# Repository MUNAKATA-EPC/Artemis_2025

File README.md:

# Artemis_2025

宗高アルテミス 2025シーズンリポジトリです。

2025シーズンはSoccer OpenLeagueに出場します。

## リポジトリについて (引用：2024シーズンリポジトリ)
・フォルダ階層をきれいにしよう  
・パス設定は相対パス基準にしよう  
・あとは動けばなんでもよし。  

## 命名規則など (一部引用：2024シーズンリポジトリ)
・各ロボットごとにプロジェクトファイルを作成しましょう。(英字表記推奨、フォルダ名に2バイト文字は嫌じゃ！！！！)  
　ex. Project_hogehugaNode

・PlatformIO等で作成されたプロジェクトフォルダの名前は (プロジェクト名)-(開発環境) にしましょう。  
　ex. hogehoge-teensy40 hugahuga-seeeduinoxiaorp2040
 
・KiCad、Fusion360などで作成されたフォルダ、ファイルの名前は一目でわかる名前にしましょう。  
　間違ってもファイル名を"unko"とかにするなよ！！！！！(戒め)

 ## 開発環境
 |種類|使用ソフト|
 |:---:|:---|
 |機体設計|Autodesk Fusion|
 |回路設計|KiCad 7.x (only use 7.x ver.)|
 |ソフト開発|Microsoft Visual Studio Code (with PlatformIO)<br>Arduino IDE<br>OpenMV IDE|

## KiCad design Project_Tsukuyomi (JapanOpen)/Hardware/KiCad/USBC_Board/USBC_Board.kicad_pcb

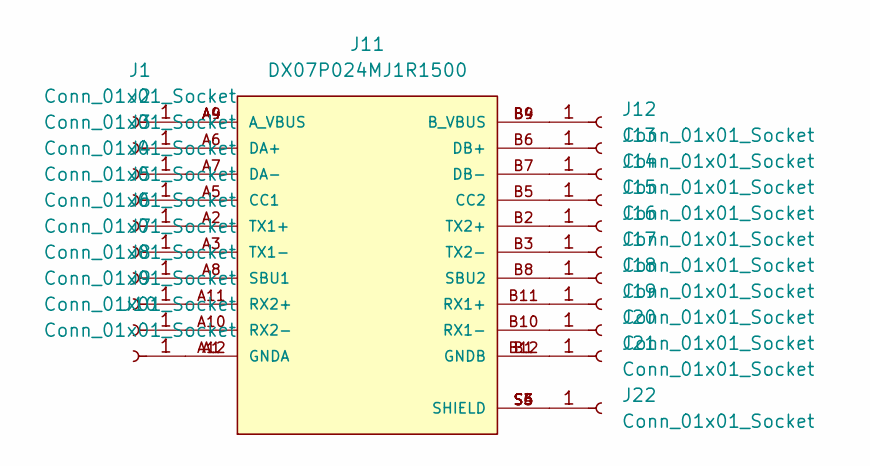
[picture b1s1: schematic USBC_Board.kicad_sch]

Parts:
J1, J2, J3, J4, J5, J6, J7, J8, J9, J10, J12, J13, J14, J15, J16, J17, J18, J19, J20, J21, J22: Conn_01x01_Socket; TestPoint_Pad_D1.0mm
J11: DX07P024MJ1R1500; JAE_DX07P024MJ1R1500; PARTREV 1.0; LCSC C134112

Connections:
unnamed: J1.1, J11.A4 (A_VBUS), J11.A9 (A_VBUS)
unnamed: J10.1, J11.A1 (GNDA), J11.A12 (GNDA)
unnamed: J4.1, J11.A5 (CC1)
unnamed: J11.B5 (CC2), J15.1
unnamed: J2.1, J11.A6 (DA+)
unnamed: J3.1, J11.A7 (DA-)
unnamed: J11.B6 (DB+), J13.1
unnamed: J11.B7 (DB-), J14.1
unnamed: J11.B11 (RX1+), J19.1
unnamed: J11.B10 (RX1-), J20.1
unnamed: J8.1, J11.A11 (RX2+)
unnamed: J9.1, J11.A10 (RX2-)
unnamed: J7.1, J11.A8 (SBU1)
unnamed: J11.B8 (SBU2), J18.1
unnamed: J5.1, J11.A2 (TX1+)
unnamed: J6.1, J11.A3 (TX1-)
unnamed: J11.B2 (TX2+), J16.1
unnamed: J11.B3 (TX2-), J17.1
unnamed: J11.B4 (B_VBUS), J11.B9 (B_VBUS), J12.1
unnamed: J11.B1 (GNDB), J11.B12 (GNDB), J21.1
unnamed: J11.S3 (SHIELD), J11.S4 (SHIELD), J11.S5 (SHIELD), J11.S6 (SHIELD), J22.1

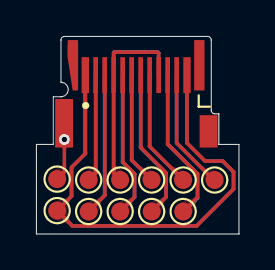
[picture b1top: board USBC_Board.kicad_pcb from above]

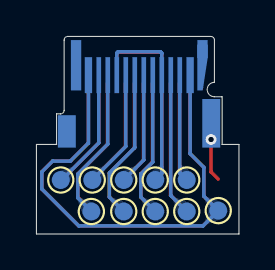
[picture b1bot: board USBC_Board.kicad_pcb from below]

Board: 2 copper layers, 11.2 x 11.0 mm, 22 parts (10 on the bottom side), 21 nets.

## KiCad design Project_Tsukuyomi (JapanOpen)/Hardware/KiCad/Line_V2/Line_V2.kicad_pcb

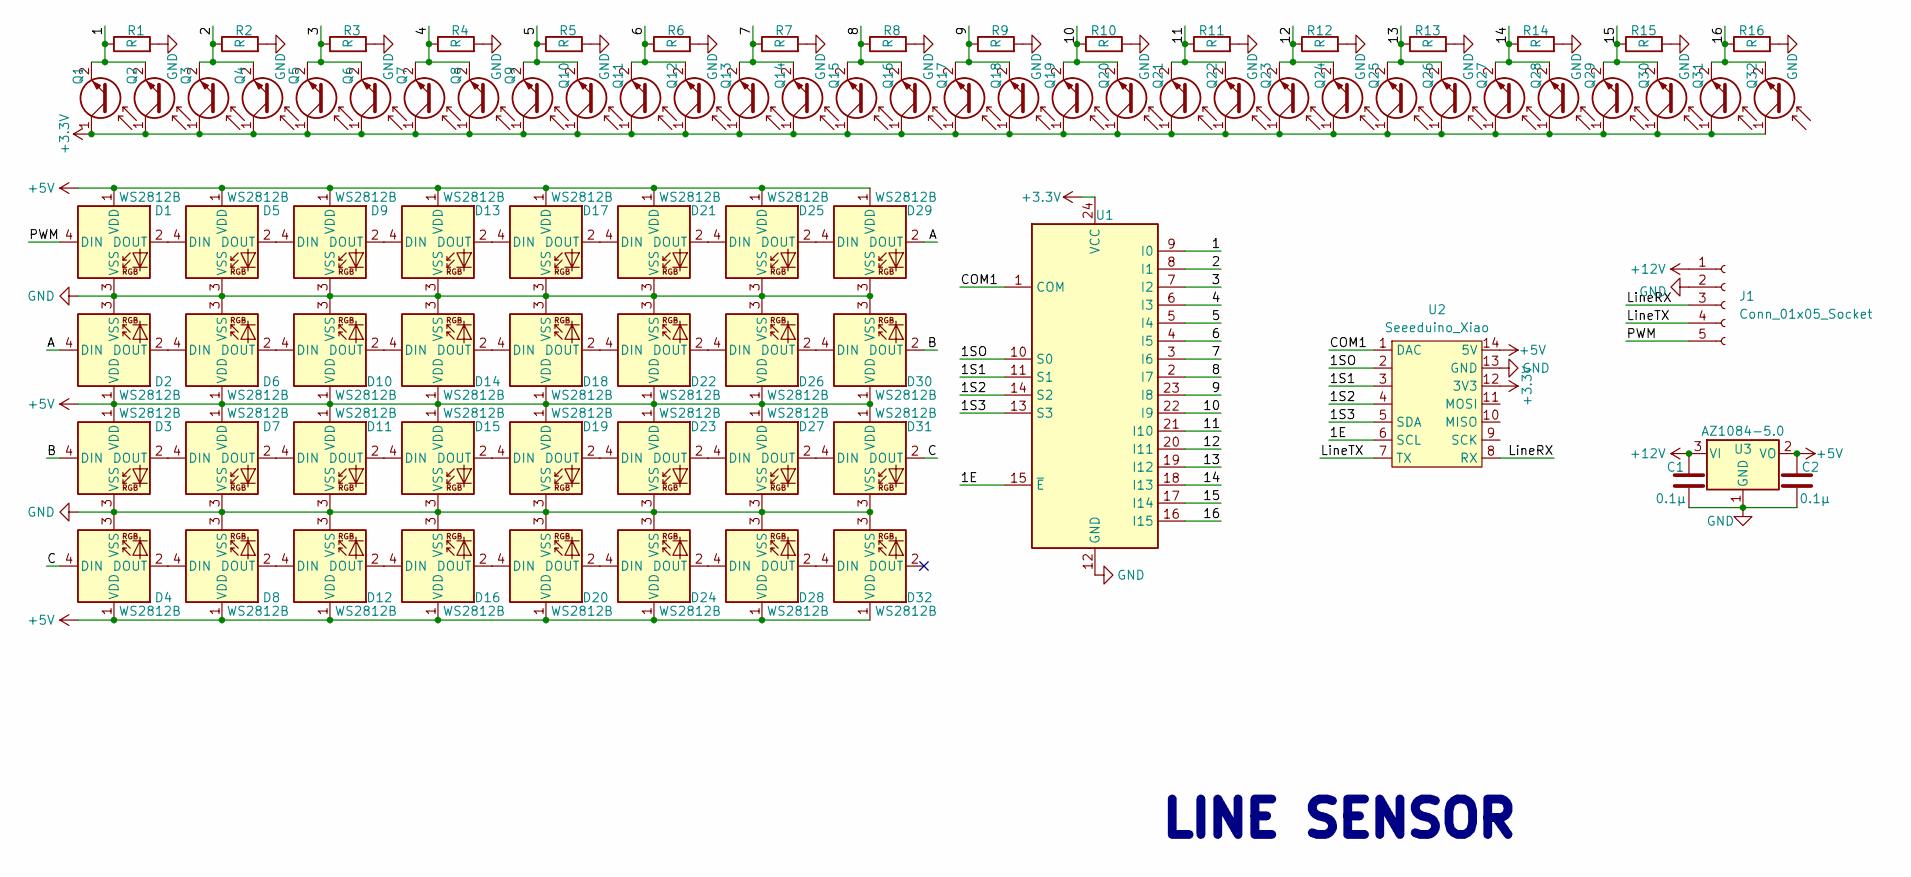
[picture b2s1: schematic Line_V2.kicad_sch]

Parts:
C1: 0.1μ; C_1210_3225Metric
C2: 0.1μ; C_0402_1005Metric; LCSC C1525
D1, D2, D3, D4, D5, D6, D7, D8, D9, D10, D11, D12, D13, D14, D15, D16, D17, D18, D19, D20, D21, D22, D23, D24, D25, D26, D27, D28, D29, D30, D31, D32: WS2812B; LED_WS2812B_PLCC4_5.0x5.0mm_P3.2mm; LCSC C965555
J1: Conn_01x05_Socket; PinHeader_1x05_P2.54mm_Vertical
Q1, Q2, Q3, Q4, Q5, Q6, Q7, Q8, Q9, Q10, Q11, Q12, Q13, Q14, Q15, Q16, Q17, Q18, Q19, Q20, Q21, Q22, Q23, Q24, Q25, Q26, Q27, Q28, Q29, Q30, Q31, Q32: Q_Photo_NPN; LED_D3.0mm
R1, R2, R3, R4, R5, R6, R7, R8, R9, R10, R11, R12, R13, R14, R15, R16: R; R_0603_1608Metric; LCSC C912493
U1: CD74HC4067SM; SSOP-24_5.3x8.2mm_P0.65mm; LCSC C98457
U2: Seeeduino_Xiao; seeeduinoXIAO
U3: AZ1084-5.0; TO-252-2

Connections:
+3.3V: Q1.1 (C), Q2.1 (C), Q3.1 (C), Q4.1 (C), Q5.1 (C), Q6.1 (C), Q7.1 (C), Q8.1 (C), Q9.1 (C), Q10.1 (C), Q11.1 (C), Q12.1 (C), Q13.1 (C), Q14.1 (C), Q15.1 (C), Q16.1 (C), Q17.1 (C), Q18.1 (C), Q19.1 (C), Q20.1 (C), Q21.1 (C), Q22.1 (C), Q23.1 (C), Q24.1 (C), Q25.1 (C), Q26.1 (C), Q27.1 (C), Q28.1 (C), Q29.1 (C), Q30.1 (C), Q31.1 (C), Q32.1 (C), U1.24 (VCC), U2.12 (3V3)
+5V: C2.2, D1.1 (VDD), D2.1 (VDD), D3.1 (VDD), D4.1 (VDD), D5.1 (VDD), D6.1 (VDD), D7.1 (VDD), D8.1 (VDD), D9.1 (VDD), D10.1 (VDD), D11.1 (VDD), D12.1 (VDD), D13.1 (VDD), D14.1 (VDD), D15.1 (VDD), D16.1 (VDD), D17.1 (VDD), D18.1 (VDD), D19.1 (VDD), D20.1 (VDD), D21.1 (VDD), D22.1 (VDD), D23.1 (VDD), D24.1 (VDD), D25.1 (VDD), D26.1 (VDD), D27.1 (VDD), D28.1 (VDD), D29.1 (VDD), D30.1 (VDD), D31.1 (VDD), D32.1 (VDD), U2.14 (5V), U3.2 (VO)
+12V: C1.2, J1.1, U3.3 (VI)
/1: Q1.2 (E), Q2.2 (E), R1.1, U1.9 (I0)
/1E: U1.15 (~E), U2.6 (SCL)
/1S1: U1.11 (S1), U2.3
/1S2: U1.14 (S2), U2.4
/1S3: U1.13 (S3), U2.5 (SDA)
/1SO: U1.10 (S0), U2.2
/2: Q3.2 (E), Q4.2 (E), R2.1, U1.8 (I1)
/3: Q5.2 (E), Q6.2 (E), R3.1, U1.7 (I2)
/4: Q7.2 (E), Q8.2 (E), R4.1, U1.6 (I3)
/5: Q9.2 (E), Q10.2 (E), R5.1, U1.5 (I4)
/6: Q11.2 (E), Q12.2 (E), R6.1, U1.4 (I5)
/7: Q13.2 (E), Q14.2 (E), R7.1, U1.3 (I6)
/8: Q15.2 (E), Q16.2 (E), R8.1, U1.2 (I7)
/9: Q17.2 (E), Q18.2 (E), R9.1, U1.23 (I8)
/10: Q19.2 (E), Q20.2 (E), R10.1, U1.22 (I9)
/11: Q21.2 (E), Q22.2 (E), R11.1, U1.21 (I10)
/12: Q23.2 (E), Q24.2 (E), R12.1, U1.20 (I11)
/13: Q25.2 (E), Q26.2 (E), R13.1, U1.19 (I12)
/14: Q27.2 (E), Q28.2 (E), R14.1, U1.18 (I13)
/15: Q29.2 (E), Q30.2 (E), R15.1, U1.17 (I14)
/16: Q31.2 (E), Q32.2 (E), R16.1, U1.16 (I15)
/A: D2.4 (DIN), D29.2 (DOUT)
/B: D3.4 (DIN), D30.2 (DOUT)
/C: D4.4 (DIN), D31.2 (DOUT)
/COM1: U1.1 (COM), U2.1 (DAC)
/LineRX: J1.3, U2.8 (RX)
/LineTX: J1.4, U2.7 (TX)
/PWM: D1.4 (DIN), J1.5
GND: C1.1, C2.1, D1.3 (VSS), D2.3 (VSS), D3.3 (VSS), D4.3 (VSS), D5.3 (VSS), D6.3 (VSS), D7.3 (VSS), D8.3 (VSS), D9.3 (VSS), D10.3 (VSS), D11.3 (VSS), D12.3 (VSS), D13.3 (VSS), D14.3 (VSS), D15.3 (VSS), D16.3 (VSS), D17.3 (VSS), D18.3 (VSS), D19.3 (VSS), D20.3 (VSS), D21.3 (VSS), D22.3 (VSS), D23.3 (VSS), D24.3 (VSS), D25.3 (VSS), D26.3 (VSS), D27.3 (VSS), D28.3 (VSS), D29.3 (VSS), D30.3 (VSS), D31.3 (VSS), D32.3 (VSS), J1.2, R1.2, R2.2, R3.2, R4.2, R5.2, R6.2, R7.2, R8.2, R9.2, R10.2, R11.2, R12.2, R13.2, R14.2, R15.2, R16.2, U1.12 (GND), U2.13 (GND), U3.1 (GND)
unnamed: D1.2 (DOUT), D5.4 (DIN)
unnamed: D2.2 (DOUT), D6.4 (DIN)
unnamed: D3.2 (DOUT), D7.4 (DIN)
unnamed: D4.2 (DOUT), D8.4 (DIN)
unnamed: D5.2 (DOUT), D9.4 (DIN)
unnamed: D6.2 (DOUT), D10.4 (DIN)
unnamed: D10.2 (DOUT), D14.4 (DIN)
unnamed: D7.2 (DOUT), D11.4 (DIN)
unnamed: D11.2 (DOUT), D15.4 (DIN)
unnamed: D8.2 (DOUT), D12.4 (DIN)
unnamed: D12.2 (DOUT), D16.4 (DIN)
unnamed: D9.2 (DOUT), D13.4 (DIN)
unnamed: D13.2 (DOUT), D17.4 (DIN)
unnamed: D14.2 (DOUT), D18.4 (DIN)
unnamed: D15.2 (DOUT), D19.4 (DIN)
unnamed: D16.2 (DOUT), D20.4 (DIN)
unnamed: D17.2 (DOUT), D21.4 (DIN)
unnamed: D18.2 (DOUT), D22.4 (DIN)
unnamed: D19.2 (DOUT), D23.4 (DIN)
unnamed: D20.2 (DOUT), D24.4 (DIN)
unnamed: D21.2 (DOUT), D25.4 (DIN)
unnamed: D22.2 (DOUT), D26.4 (DIN)
unnamed: D23.2 (DOUT), D27.4 (DIN)
unnamed: D24.2 (DOUT), D28.4 (DIN)
unnamed: D25.2 (DOUT), D29.4 (DIN)
unnamed: D26.2 (DOUT), D30.4 (DIN)
unnamed: D27.2 (DOUT), D31.4 (DIN)
unnamed: D28.2 (DOUT), D32.4 (DIN)

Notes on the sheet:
LINE SENSOR

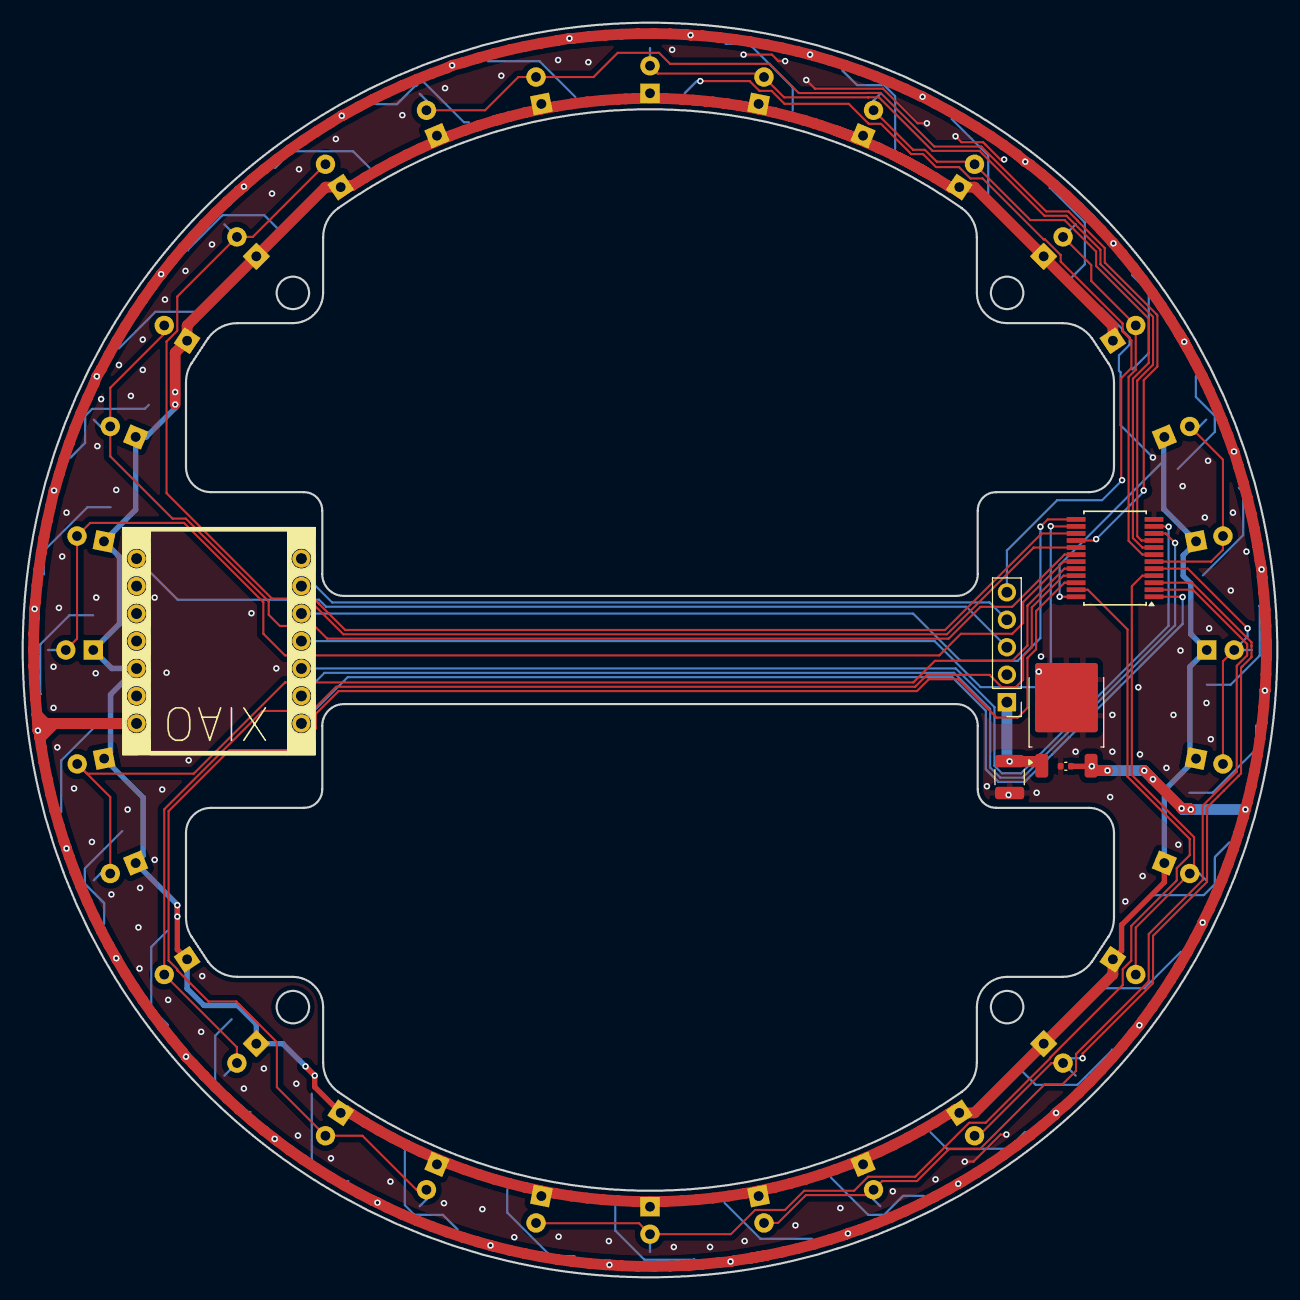
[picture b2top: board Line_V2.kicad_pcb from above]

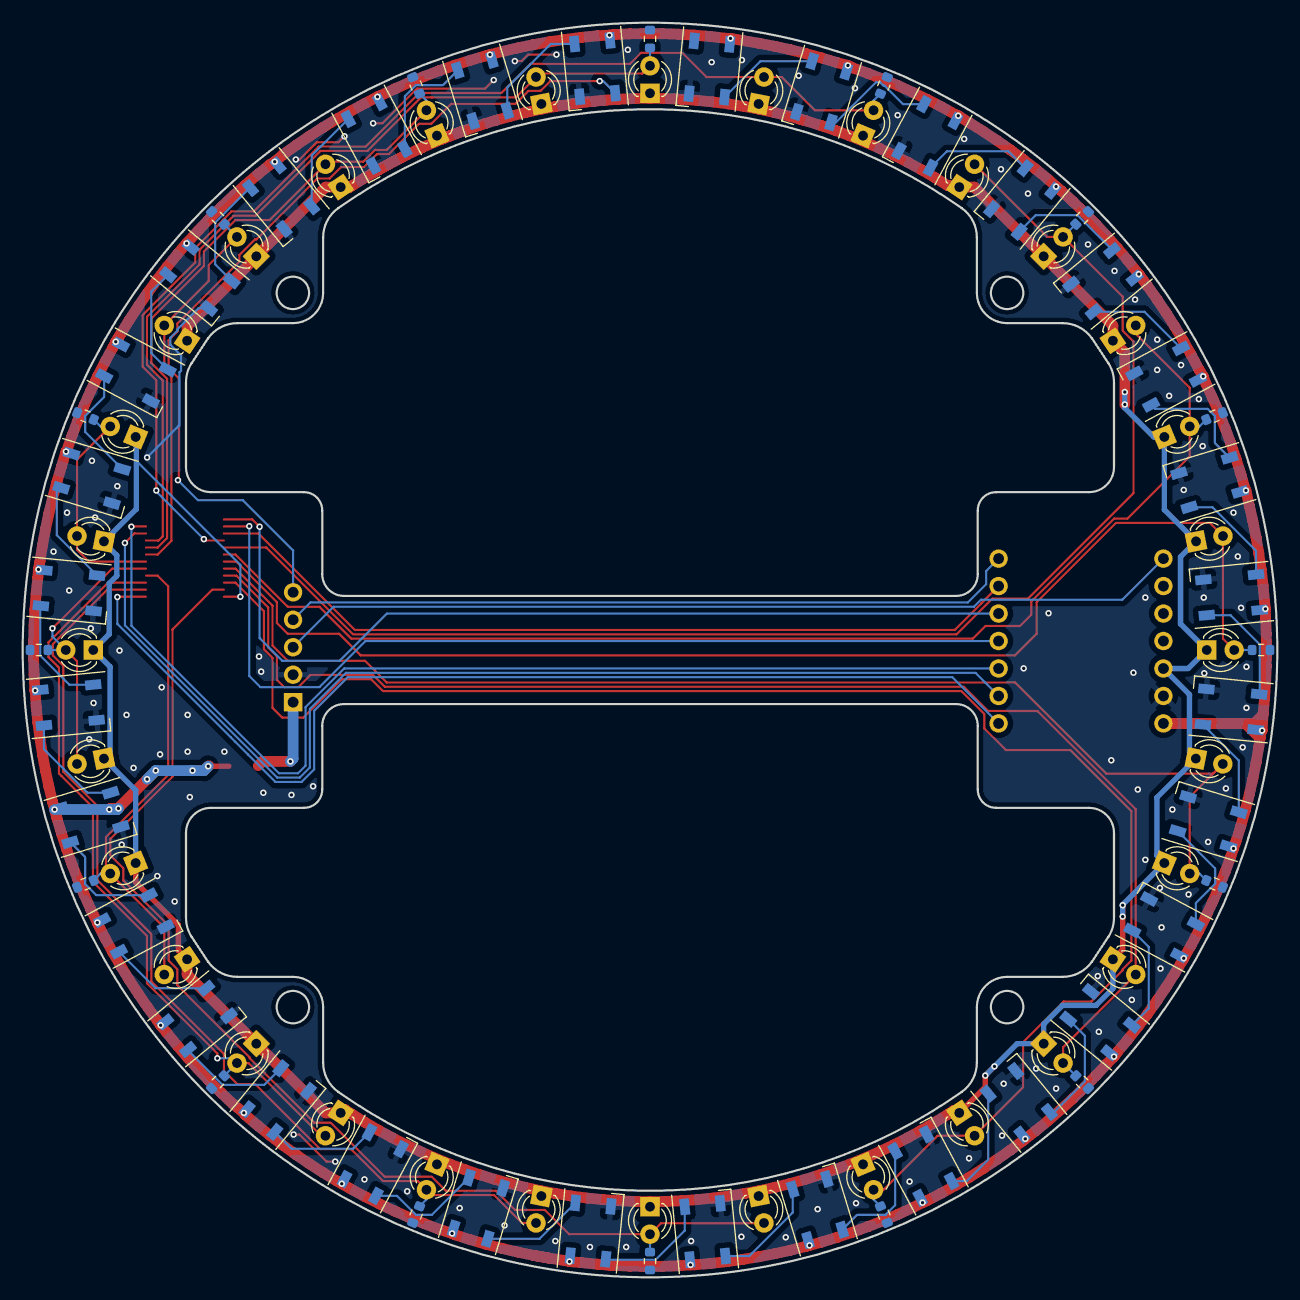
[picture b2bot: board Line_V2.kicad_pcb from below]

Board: 2 copper layers, 116.0 x 116.0 mm, 86 parts (80 on the bottom side), 60 nets.

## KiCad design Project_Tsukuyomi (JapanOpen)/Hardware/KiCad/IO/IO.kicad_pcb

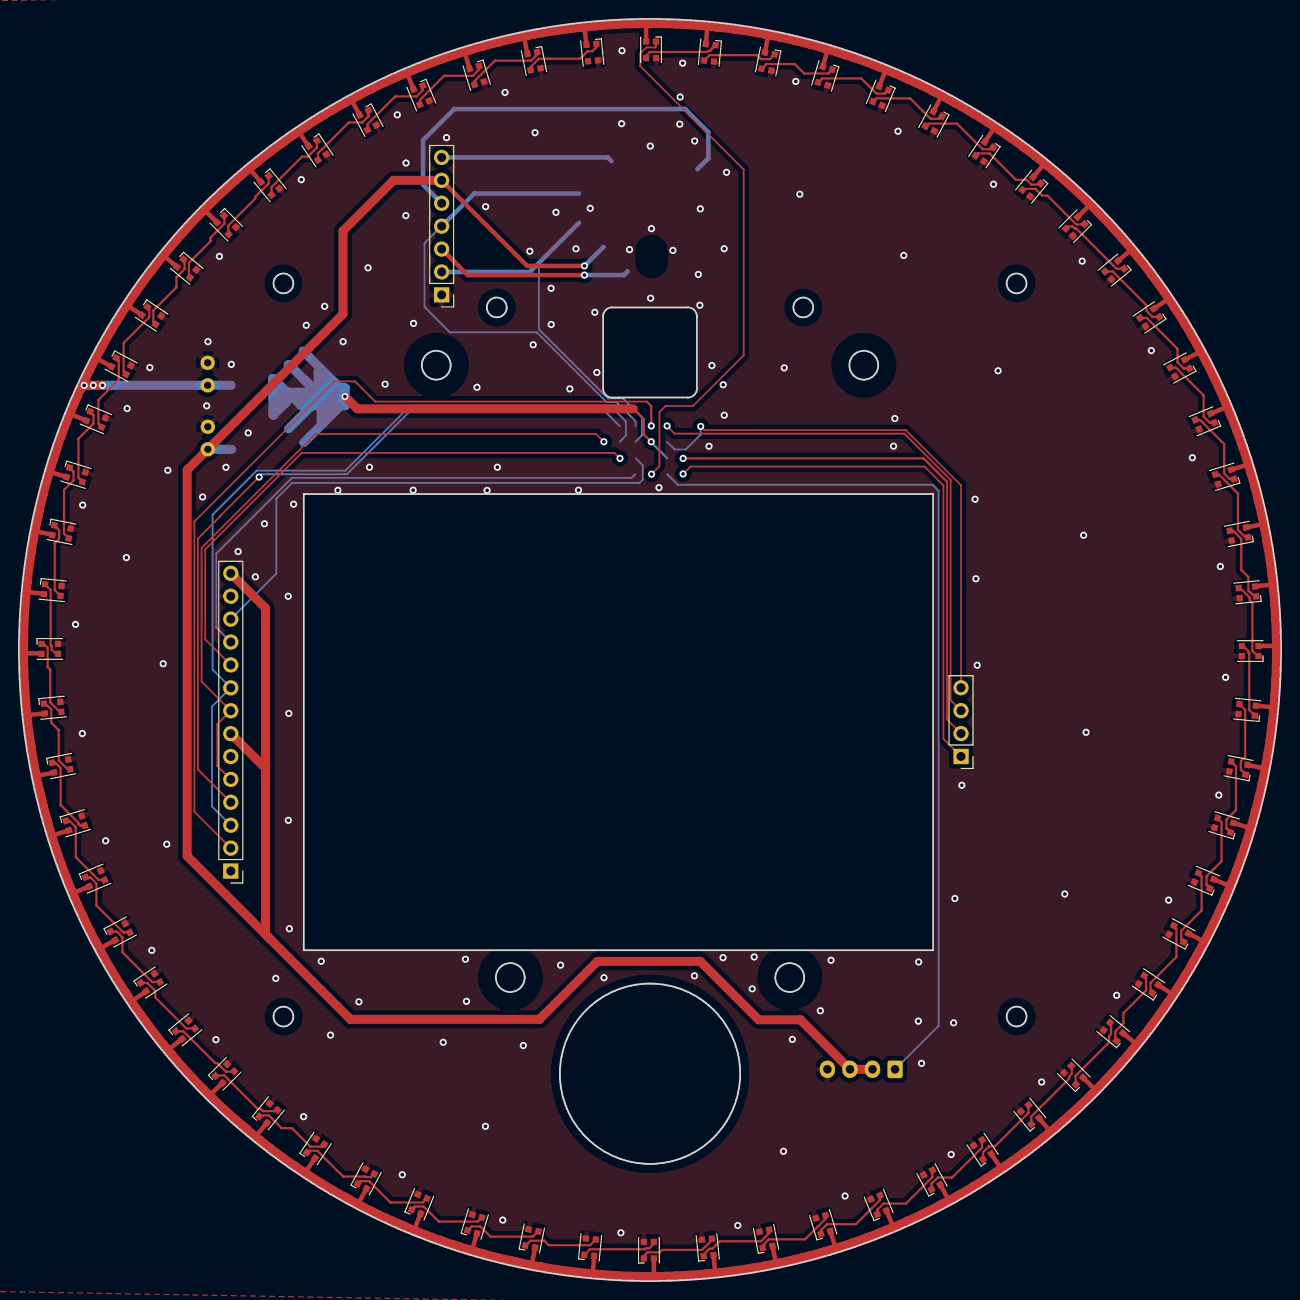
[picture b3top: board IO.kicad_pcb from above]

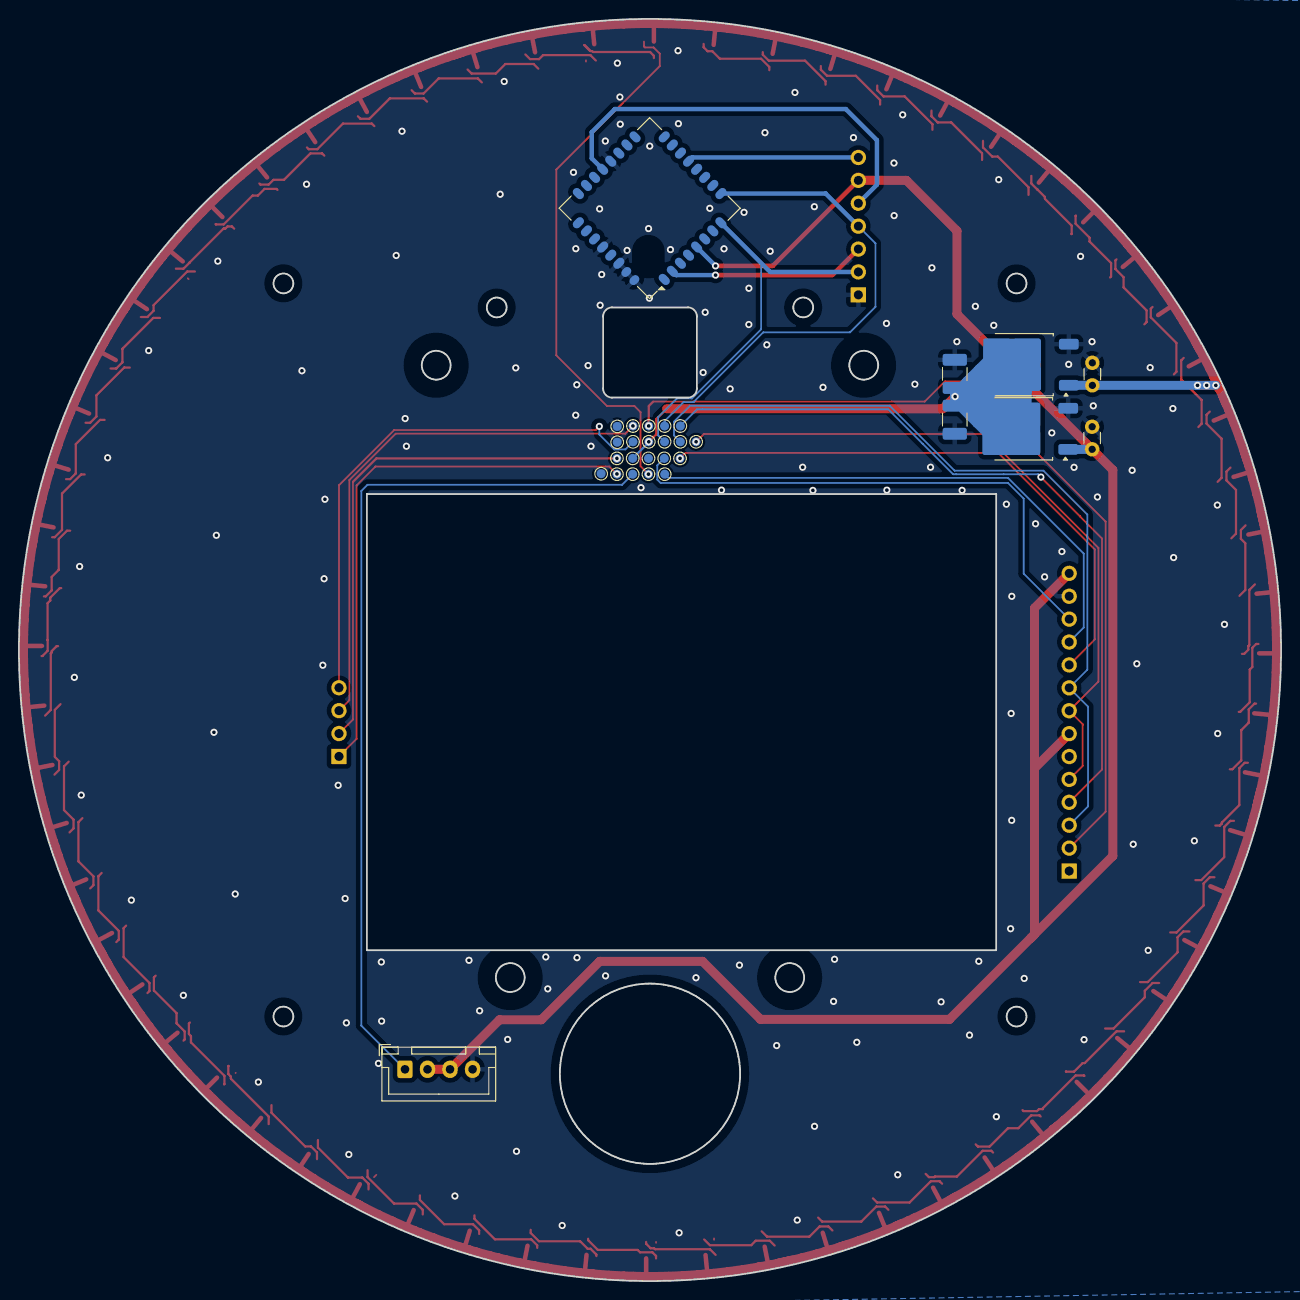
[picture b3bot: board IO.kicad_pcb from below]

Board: 2 copper layers, 140.0 x 140.0 mm, 96 parts (29 on the bottom side), 85 nets.

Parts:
C1, C3: C; C_1210_3225Metric_Pad1.33x2.70mm_HandSolder
C2, C4: C; C_Disc_D3.0mm_W1.6mm_P2.50mm
D1, D2, D3, D4, D5, D6, D7, D8, D9, D10, D11, D12, D13, D14, D15, D16, D17, D18, D19, D20, D21, D22, D23, D24, D25, D26, D27, D28, D29, D30, D31, D32, D33, D34, D35, D36, D37, D38, D39, D40, D41, D42, D43, D44, D45, D46, D47, D48, D49, D50, D51, D52, D53, D54, D55, D56, D57, D58, D59, D60, D61, D62, D63, D64: WS2812B; LED_WS2812B-2020_PLCC4_2.0x2.0mm
J1: Conn_01x14_Socket; PinHeader_1x14_P2.54mm_Vertical
J1#2, J2#2, J3#2, J4, J5#2, J6, J7, J8, J9, J10, J12, J13, J14, J15, J16, J17, J18, J19, J20, J21, J22: Conn_01x01_Socket; TestPoint_Pad_D1.0mm
J2: Conn_01x04_Socket; JST_XH_B4B-XH-A_1x04_P2.50mm_Vertical
J3: Conn_01x04_Socket; PinHeader_1x04_P2.54mm_Vertical
J5: Conn_01x07_Socket; PinHeader_1x07_P2.54mm_Vertical
U1: AZ1084-3.3; TO-252-2
U2: AZ1084-5.0; TO-252-2
U3: TWE-L-WX; MonoWireless_TWE-L-WX

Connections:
+3.3V: C2.1, J1.7, J1.14, J2.2, J2.3, J5.6, U1.2 (VO), U3.5 (VCC)
+5V: C4.1, D1.1 (VDD), D2.1 (VDD), D3.1 (VDD), D4.1 (VDD), D5.1 (VDD), D6.1 (VDD), D7.1 (VDD), D8.1 (VDD), D9.1 (VDD), D10.1 (VDD), D11.1 (VDD), D12.1 (VDD), D13.1 (VDD), D14.1 (VDD), D15.1 (VDD), D16.1 (VDD), D17.1 (VDD), D18.1 (VDD), D19.1 (VDD), D20.1 (VDD), D21.1 (VDD), D22.1 (VDD), D23.1 (VDD), D24.1 (VDD), D25.1 (VDD), D26.1 (VDD), D27.1 (VDD), D28.1 (VDD), D29.1 (VDD), D30.1 (VDD), D31.1 (VDD), D32.1 (VDD), D33.1 (VDD), D34.1 (VDD), D35.1 (VDD), D36.1 (VDD), D37.1 (VDD), D38.1 (VDD), D39.1 (VDD), D40.1 (VDD), D41.1 (VDD), D42.1 (VDD), D43.1 (VDD), D44.1 (VDD), D45.1 (VDD), D46.1 (VDD), D47.1 (VDD), D48.1 (VDD), D49.1 (VDD), D50.1 (VDD), D51.1 (VDD), D52.1 (VDD), D53.1 (VDD), D54.1 (VDD), D55.1 (VDD), D56.1 (VDD), D57.1 (VDD), D58.1 (VDD), D59.1 (VDD), D60.1 (VDD), D61.1 (VDD), D62.1 (VDD), D63.1 (VDD), D64.1 (VDD), U2.2 (VO)
+12V: C1.1, C3.1, J1#2.1, J12.1, U1.3 (VI), U2.3 (VI)
/A: D2.4 (DIN), D57.2 (DOUT)
/B: D3.4 (DIN), D58.2 (DOUT)
/C: D4.4 (DIN), D59.2 (DOUT)
/CS: J1.12, J15.1
/D: D5.4 (DIN), D60.2 (DOUT)
/DC: J1.10, J16.1
/E: D6.4 (DIN), D61.2 (DOUT)
/F: D7.4 (DIN), D62.2 (DOUT)
/G: D8.4 (DIN), D63.2 (DOUT)
/MISO: J1.2, J4.1
/MOSI: J1.3, J1.9, J7.1
/PRG: J5.3, U3.2 (DO1/PWM3)
/PWM: D1.4 (DIN), J13.1
/RESET: J1.11, J17.1
/RST: J5.5, U3.21 (~RESET)
/RXD: J3#2.1, J5.4, U3.9 (DIO7/RX)
/SCK: J1.5, J1.8, J8.1
/SD＿CS: J3.4, J5#2.1
/SD＿MISO: J3.2, J19.1
/SD＿MOSI: J3.3, J6.1
/SD＿SCK: J3.1, J20.1
/SET: J5.7, U3.13 (DIO12/DI1)
/START: J2.1, J18.1
/TXD: J2#2.1, J5.2, U3.8 (DIO6/TX)
/T_CS: J1.4, J9.1
GND: C1.2, C2.2, C3.2, C4.2, D1.3 (VSS), D2.3 (VSS), D3.3 (VSS), D4.3 (VSS), D5.3 (VSS), D6.3 (VSS), D7.3 (VSS), D8.3 (VSS), D9.3 (VSS), D10.3 (VSS), D11.3 (VSS), D12.3 (VSS), D13.3 (VSS), D14.3 (VSS), D15.3 (VSS), D16.3 (VSS), D17.3 (VSS), D18.3 (VSS), D19.3 (VSS), D20.3 (VSS), D21.3 (VSS), D22.3 (VSS), D23.3 (VSS), D24.3 (VSS), D25.3 (VSS), D26.3 (VSS), D27.3 (VSS), D28.3 (VSS), D29.3 (VSS), D30.3 (VSS), D31.3 (VSS), D32.3 (VSS), D33.3 (VSS), D34.3 (VSS), D35.3 (VSS), D36.3 (VSS), D37.3 (VSS), D38.3 (VSS), D39.3 (VSS), D40.3 (VSS), D41.3 (VSS), D42.3 (VSS), D43.3 (VSS), D44.3 (VSS), D45.3 (VSS), D46.3 (VSS), D47.3 (VSS), D48.3 (VSS), D49.3 (VSS), D50.3 (VSS), D51.3 (VSS), D52.3 (VSS), D53.3 (VSS), D54.3 (VSS), D55.3 (VSS), D56.3 (VSS), D57.3 (VSS), D58.3 (VSS), D59.3 (VSS), D60.3 (VSS), D61.3 (VSS), D62.3 (VSS), D63.3 (VSS), D64.3 (VSS), J1.13, J2.4, J5.1, J10.1, J21.1, J22.1, U1.1 (GND), U2.1 (GND), U3.20 (GND), U3.28 (GND), U3.30 (GND), U3.31 (GND), U3.32 (GND)
unnamed: D1.2 (DOUT), D9.4 (DIN)
unnamed: D2.2 (DOUT), D10.4 (DIN)
unnamed: D10.2 (DOUT), D18.4 (DIN)
unnamed: D3.2 (DOUT), D11.4 (DIN)
unnamed: D11.2 (DOUT), D19.4 (DIN)
unnamed: D4.2 (DOUT), D12.4 (DIN)
unnamed: D12.2 (DOUT), D20.4 (DIN)
unnamed: D5.2 (DOUT), D13.4 (DIN)
unnamed: D13.2 (DOUT), D21.4 (DIN)
unnamed: D6.2 (DOUT), D14.4 (DIN)
unnamed: D14.2 (DOUT), D22.4 (DIN)
unnamed: D7.2 (DOUT), D15.4 (DIN)
unnamed: D15.2 (DOUT), D23.4 (DIN)
unnamed: D8.2 (DOUT), D16.4 (DIN)
unnamed: D16.2 (DOUT), D24.4 (DIN)
unnamed: D9.2 (DOUT), D17.4 (DIN)
unnamed: D17.2 (DOUT), D25.4 (DIN)
unnamed: D18.2 (DOUT), D26.4 (DIN)
unnamed: D19.2 (DOUT), D27.4 (DIN)
unnamed: D20.2 (DOUT), D28.4 (DIN)
unnamed: D21.2 (DOUT), D29.4 (DIN)
unnamed: D22.2 (DOUT), D30.4 (DIN)
unnamed: D23.2 (DOUT), D31.4 (DIN)
unnamed: D24.2 (DOUT), D32.4 (DIN)
unnamed: D25.2 (DOUT), D33.4 (DIN)
unnamed: D26.2 (DOUT), D34.4 (DIN)
unnamed: D27.2 (DOUT), D35.4 (DIN)
unnamed: D28.2 (DOUT), D36.4 (DIN)
unnamed: D29.2 (DOUT), D37.4 (DIN)
unnamed: D30.2 (DOUT), D38.4 (DIN)
unnamed: D31.2 (DOUT), D39.4 (DIN)
unnamed: D32.2 (DOUT), D40.4 (DIN)
unnamed: D33.2 (DOUT), D41.4 (DIN)
unnamed: D34.2 (DOUT), D42.4 (DIN)
unnamed: D35.2 (DOUT), D43.4 (DIN)
unnamed: D36.2 (DOUT), D44.4 (DIN)
unnamed: D37.2 (DOUT), D45.4 (DIN)
unnamed: D38.2 (DOUT), D46.4 (DIN)
unnamed: D39.2 (DOUT), D47.4 (DIN)
unnamed: D40.2 (DOUT), D48.4 (DIN)
unnamed: D41.2 (DOUT), D49.4 (DIN)
unnamed: D42.2 (DOUT), D50.4 (DIN)
unnamed: D43.2 (DOUT), D51.4 (DIN)
unnamed: D44.2 (DOUT), D52.4 (DIN)
unnamed: D45.2 (DOUT), D53.4 (DIN)
unnamed: D46.2 (DOUT), D54.4 (DIN)
unnamed: D47.2 (DOUT), D55.4 (DIN)
unnamed: D48.2 (DOUT), D56.4 (DIN)
unnamed: D49.2 (DOUT), D57.4 (DIN)
unnamed: D50.2 (DOUT), D58.4 (DIN)
unnamed: D51.2 (DOUT), D59.4 (DIN)
unnamed: D52.2 (DOUT), D60.4 (DIN)
unnamed: D53.2 (DOUT), D61.4 (DIN)
unnamed: D54.2 (DOUT), D62.4 (DIN)
unnamed: D55.2 (DOUT), D63.4 (DIN)
unnamed: D56.2 (DOUT), D64.4 (DIN)

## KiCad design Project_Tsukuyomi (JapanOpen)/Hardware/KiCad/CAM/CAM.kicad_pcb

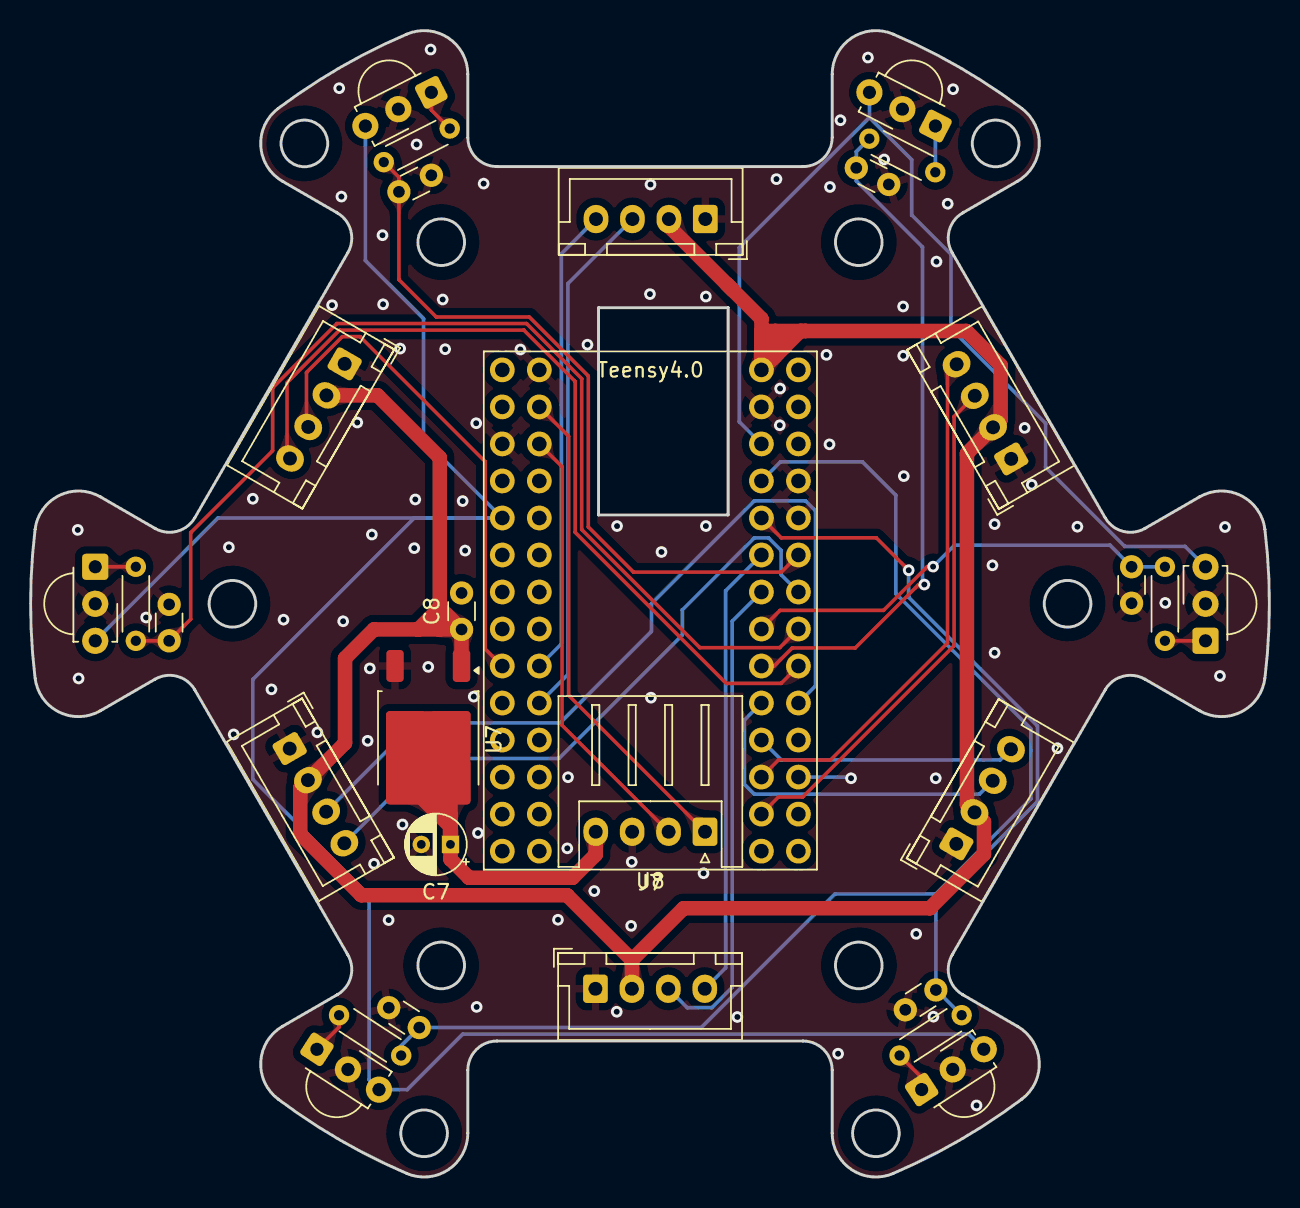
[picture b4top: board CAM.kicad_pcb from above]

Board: 2 copper layers, 85.0 x 78.7 mm, 29 parts (0 on the bottom side), 30 nets.

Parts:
C1, C2, C3, C4, C5, C6: C_Small; C_Disc_D3.0mm_W1.6mm_P2.50mm
C7: C; CP_Radial_D4.0mm_P2.00mm
C8: C; C_Disc_D3.0mm_W1.6mm_P2.50mm
J1, J2, J3, J4, J5, J6: Conn_01x04_Socket; JST_XH_B4B-XH-A_1x04_P2.50mm_Vertical
J7: Conn_01x04_Socket; JST_XH_S4B-XH-A_1x04_P2.50mm_Horizontal
R1, R2, R3, R4, R5, R6: R; R_Axial_DIN0204_L3.6mm_D1.6mm_P5.08mm_Horizontal
U1, U2, U3, U4, U5, U6: TSSP58P38; Vishay_MINICAST-3Pin
U7: AZ1084-5.0; TO-252-2
U8: Teensy4.0; Teensy_Brakeout

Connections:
+3.3V: U1.3 (Vs), U2.3 (Vs), U3.3 (Vs), U4.3 (Vs), U5.3 (Vs), U6.3 (Vs), U8.31 (3V3)
+5V: C8.1, J1.2, J2.2, J3.2, J4.2, J5.2, J6.2, U7.2 (VO), U8.33 (VIN)
+12V: C7.1, J7.4, U7.3 (VI)
/CAM1RX: J1.4, U8.9 (7_RX2_OUT1A)
/CAM1TX: J1.3, U8.10 (8_TX2_IN1)
/CAM2RX: J2.4, U8.22 (15_A1_RX3_SPDIF_IN)
/CAM2TX: J2.3, U8.21 (14_A0_TX3_SPDIF_OUT)
/CAM3RX: J3.4, U8.23 (16_A2_RX4_SCL1)
/CAM3TX: J3.3, U8.24 (17_A3_TX4_SDA1)
/CAM4RX: J4.4, U8.28 (21_A7_RX5_BCLK1)
/CAM4TX: J4.3, U8.27 (20_A6_TX5_LRCLK1)
/CAM5RX: J5.4, U8.36 (25_A11_RX6_SDA2)
/CAM5TX: J5.3, U8.35 (24_A10_TX6_SCL2)
/CAM6RX: J6.4, U8.39 (28_RX7)
/CAM6TX: J6.3, U8.40 (29_TX7)
/CAMRX: J7.2, U8.3 (1_TX1_CTX2_MISO1)
/CAMTX: J7.1, U8.2 (0_RX1_CRX2_CS1)
/IR1: C1.1, R1.2, U8.25 (18_A4_SDA0)
/IR2: C2.1, R2.2, U8.26 (19_A5_SCL0)
/IR3: C3.1, R3.2, U8.29 (22_A8_CTX1)
/IR4: C4.1, R4.2, U8.30 (23_A9_CRX1_MCLK1)
/IR5: C5.1, R5.2, U8.37 (26_A12_MOSI1)
/IR6: C6.1, R6.2, U8.38 (27_A13_SCK1)
GND: C1.2, C2.2, C3.2, C4.2, C5.2, C6.2, C7.2, C8.2, J1.1, J2.1, J3.1, J4.1, J5.1, J6.1, J7.3, U1.2 (GND), U2.2 (GND), U3.2 (GND), U4.2 (GND), U5.2 (GND), U6.2 (GND), U7.1 (GND), U8.1 (GND)
unnamed: R1.1, U1.1 (OUT)
unnamed: R2.1, U2.1 (OUT)
unnamed: R3.1, U3.1 (OUT)
unnamed: R4.1, U4.1 (OUT)
unnamed: R5.1, U5.1 (OUT)
unnamed: R6.1, U6.1 (OUT)

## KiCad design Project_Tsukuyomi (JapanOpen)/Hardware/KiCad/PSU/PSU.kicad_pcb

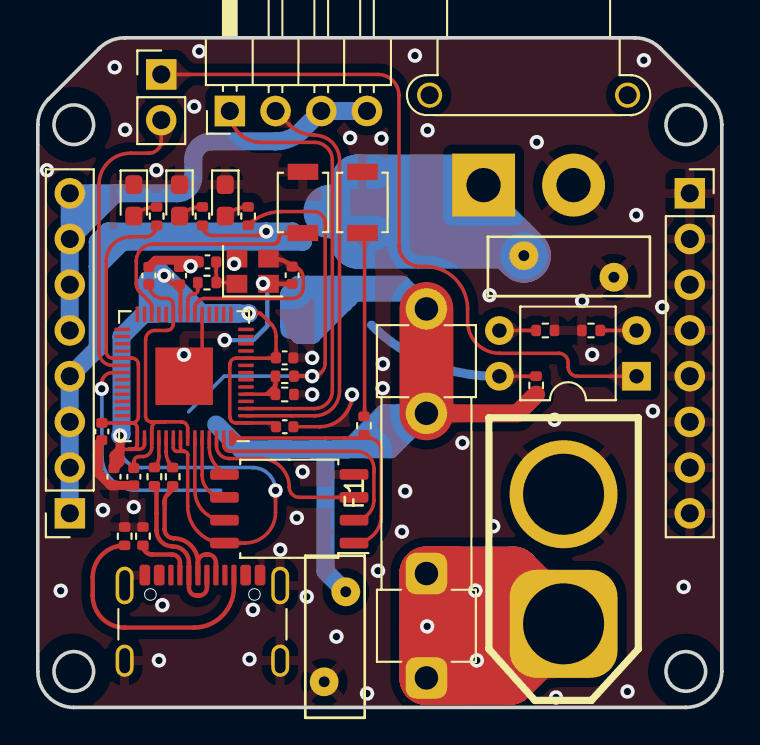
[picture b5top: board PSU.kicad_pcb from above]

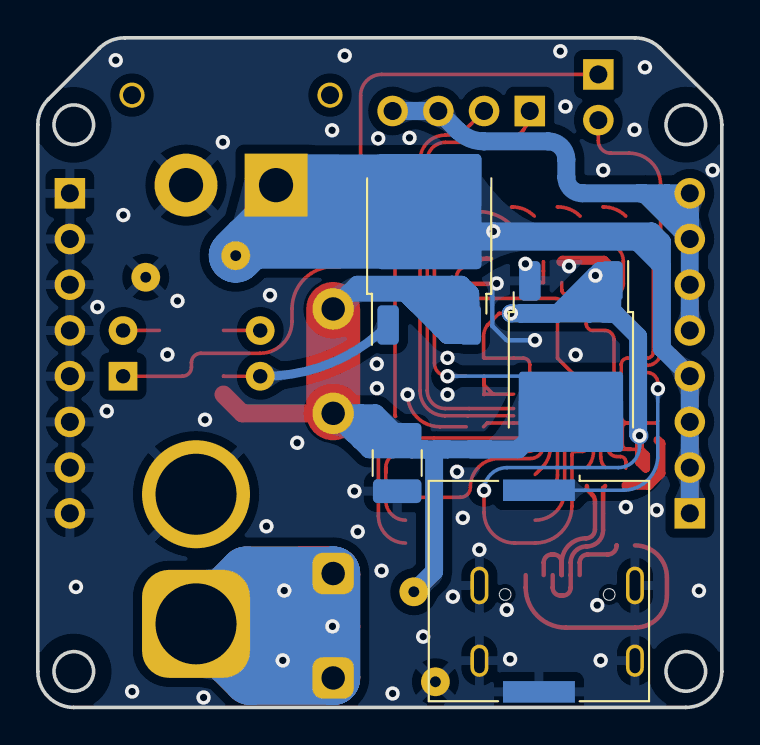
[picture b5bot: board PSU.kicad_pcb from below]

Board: 2 copper layers, 38.0 x 37.2 mm, 46 parts (4 on the bottom side), 36 nets.

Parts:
BT1: Battery; AMASS_XT60-M_1x02_P7.20mm_Vertical
BZ1: Buzzer; Buzzer_Murata_PKLCS1212E
C1, C2, C6, C7, C8, C9, C11: 0.1μ; C_0402_1005Metric
C4, C5: C_Small; C_0402_1005Metric
C10: 47μ; C_1210_3225Metric_Pad1.33x2.70mm_HandSolder
D1, D2, D3: LED; LED_0603_1608Metric_Pad1.05x0.95mm_HandSolder
F1: Fuse15A; Fuseholder_Clip-5x20mm_Littelfuse_520_Inline_P20.50x5.80mm_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
J1: USB_C_Receptacle_USB2.0; USB_C_Receptacle_GCT_USB4105-xx-A_16P_TopMnt_Horizontal
J2, J3: Conn_01x08_Socket; PinSocket_1x08_P2.54mm_Vertical
J4: Conn_01x04_Socket; PinHeader_1x04_P2.54mm_Horizontal
J5: Conn_01x02_Socket; AMASS_XT30PW-F_1x02_P2.50mm_Horizontal
J6: Conn_01x02_Socket; PinHeader_1x02_P2.54mm_Vertical
Q1: PMOS; TO-252-2
R1, R2, R3, R4, R9, R15, R16: 1k; R_0402_1005Metric
R5: 100; R_0402_1005Metric
R8: 3k; R_0402_1005Metric
R10, R11: 5.1k; R_0402_1005Metric
R12, R13: 27; R_0402_1005Metric
R14: 330; R_0402_1005Metric
RV1, RV2: Varistor; RV_Disc_D9mm_W3.3mm_P5mm
SW1, SW2: SW_Push; SW_SPST_B3U-1000P
U1: W25Q128JVS; SOIC-8_5.23x5.23mm_P1.27mm
U2: RP2040; QFN-56-1EP_7x7mm_P0.4mm_EP3.2x3.2mm
U3: SFH617A-1; DIP-4_W7.62mm
U4: AZ1084-5.0; TO-252-2
Y1: Crystal_GND24; Crystal_SMD_2520-4Pin_2.5x2.0mm

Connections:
+1V1: C1.2, C2.2, U2.23 (DVDD), U2.45 (VREG_VOUT), U2.50 (DVDD)
+3.3V: C6.2, C7.2, C8.2, C9.2, C11.1, R5.1, U1.8 (VCC), U2.1 (IOVDD), U2.10 (IOVDD), U2.22 (IOVDD), U2.33 (IOVDD), U2.42 (IOVDD), U2.43 (ADC_AVDD), U2.44 (VREG_IN), U2.48 (USB_VDD), U2.49 (IOVDD), U4.2 (VO)
+12V: J2.1, J2.2, J2.3, J2.4, J5.1, Q1.1 (D), R4.1, RV2.1
+48V: J2.5, J2.6, J2.7, J2.8, J4.3, J4.4
/BOOT: R1.1, SW2.1
/D+: R13.2, U2.47 (USB_DP)
/D-: R12.2, U2.46 (USB_DM)
/FET: J6.1, U3.1
/RUN: SW1.1, U2.26 (RUN)
/SW: J6.2, U2.34 (GPIO22)
/Temp+12v: C10.1, F1.2, Q1.3 (S), R3.1, R8.1, R16.1, RV1.1, U4.3 (VI)
/UART_RX: J4.2, U2.2 (GPIO0)
/UART_TX: J4.1, U2.3 (GPIO1)
/voltage: R8.2, R9.1, U2.5 (GPIO3)
GND: BT1.2 (-), BZ1.2 (+), C1.1, C2.1, C4.2, C5.1, C6.1, C7.1, C8.1, C9.1, C10.2, C11.2, D1.1 (K), D2.1 (K), D3.1 (K), J1.A1 (GND), J1.A12 (GND), J1.B1 (GND), J1.B12 (GND), J1.S1 (SHIELD), J3.1, J3.2, J3.3, J3.4, J3.5, J3.6, J3.7, J3.8, J5.2, R9.2, R10.2, R11.2, R14.1, R15.1, RV1.2, RV2.2, SW1.2, SW2.2, U1.4 (GND), U2.19 (TESTEN), U2.57 (GND), U4.1 (GND), Y1.2, Y1.4
unnamed: BT1.1 (+), F1.1
unnamed: BZ1.1 (-), U2.35 (GPIO23)
unnamed: C5.2, R2.2, Y1.1
unnamed: D1.2 (A), R3.2
unnamed: D2.2 (A), R4.2
unnamed: D3.2 (A), R5.2
unnamed: J1.A5 (CC1), R10.1
unnamed: J1.B5 (CC2), R11.1
unnamed: J1.A6 (D+), J1.B6 (D+), R13.1
unnamed: J1.A7 (D-), J1.B7 (D-), R12.1
unnamed: Q1.2 (G), R16.2, U3.4
unnamed: R14.2, U3.2
unnamed: R15.2, U3.3
unnamed: U1.6 (CLK), U2.52 (QSPI_SCLK)
unnamed: U1.5 (DI(IO0)), U2.53 (QSPI_SD0)
unnamed: U1.2 (DO(IO1)), U2.55 (QSPI_SD1)
unnamed: U1.3 (IO2), U2.54 (QSPI_SD2)
unnamed: U1.7 (IO3), U2.51 (QSPI_SD3)
unnamed: R1.2, U1.1 (~CS), U2.56 (QSPI_SS)
unnamed: C4.1, U2.20 (XIN), Y1.3
unnamed: R2.1, U2.21 (XOUT)
